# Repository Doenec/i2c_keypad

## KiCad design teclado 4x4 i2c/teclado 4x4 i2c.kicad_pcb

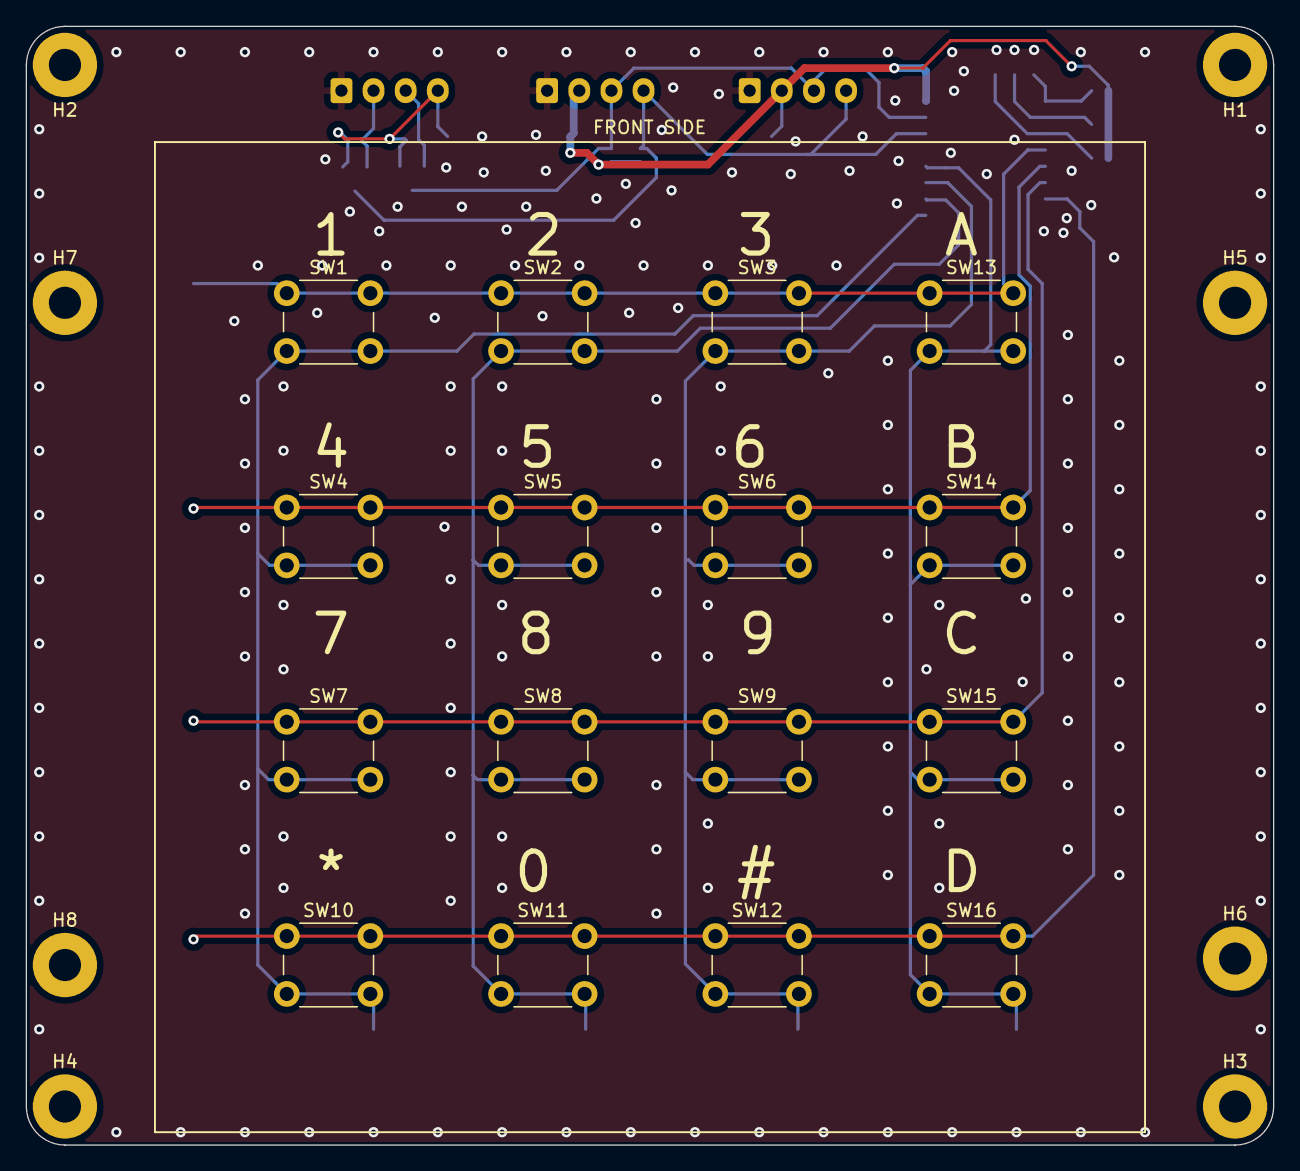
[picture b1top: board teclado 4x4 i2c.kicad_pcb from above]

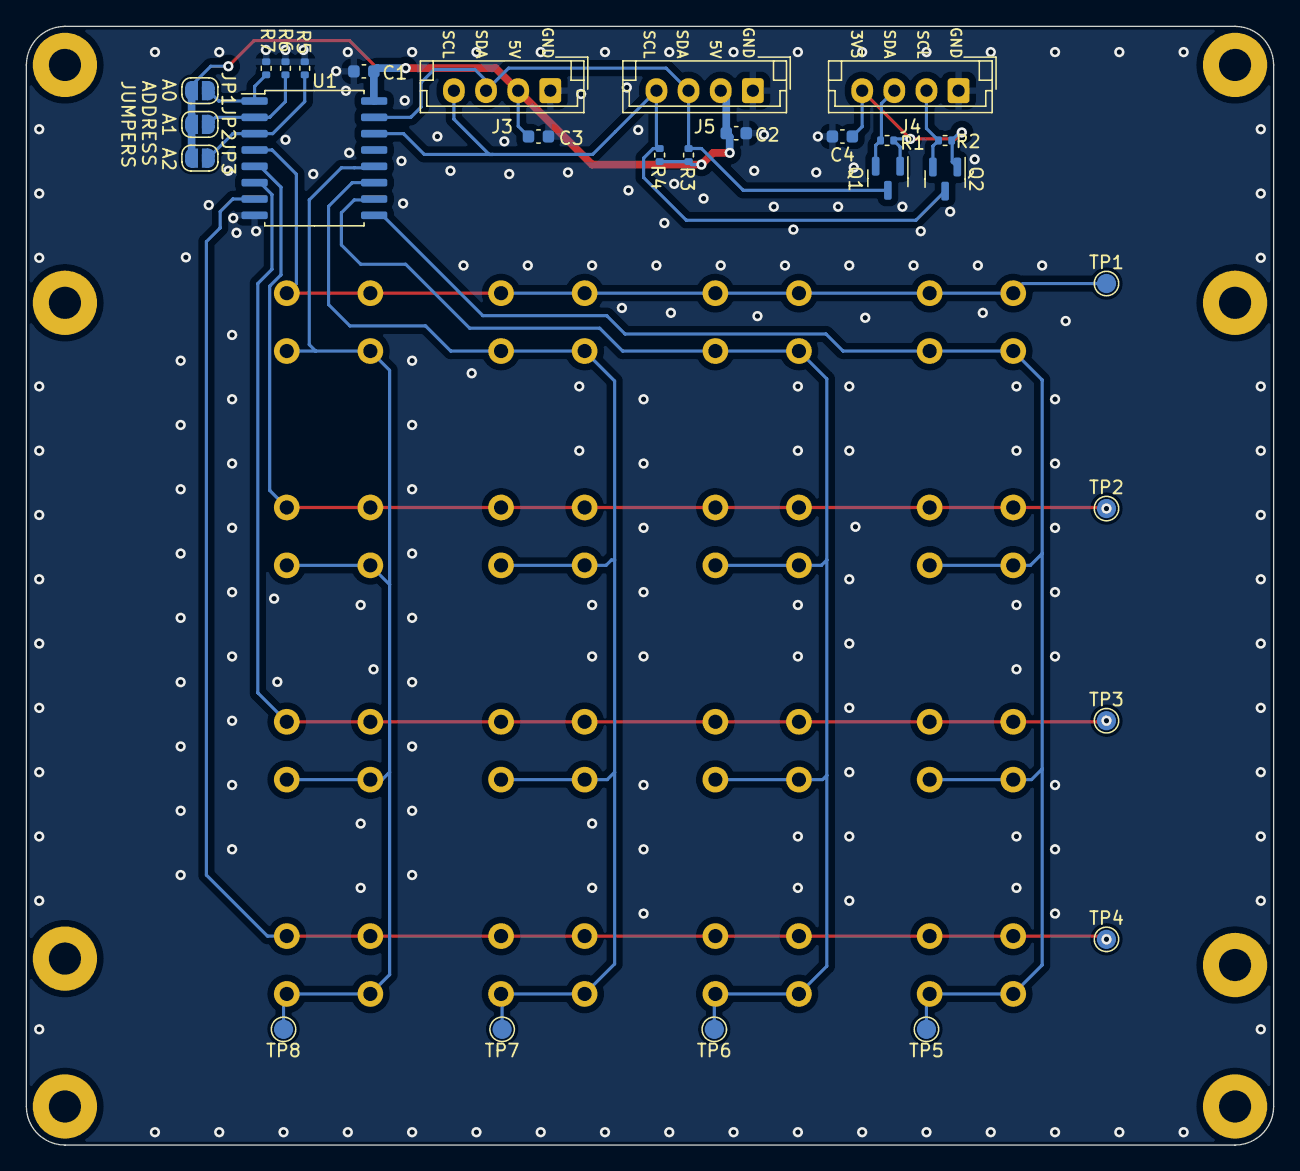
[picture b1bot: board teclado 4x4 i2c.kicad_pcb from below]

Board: 2 copper layers, 97.0 x 87.0 mm, 52 parts (28 on the bottom side), 18 nets.

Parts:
C1, C2, C3, C4: 100nF; C_0603_1608Metric
H1, H2, H3, H4, H5, H6, H7, H8: MountingHole; MountingHole_2.5mm_Pad
J3, J4, J5: I2C; JST_EH_B4B-EH-A_1x04_P2.50mm_Vertical
JP1, JP2, JP3: ADDR; SolderJumper-2_P1.3mm_Open_RoundedPad1.0x1.5mm
Q1, Q2: 2N7002; SOT-23
R1, R2, R3, R4, R5, R6, R7: 10K; R_0402_1005Metric
SW1: B1; SW_PUSH_6mm_H4.3mm
SW2: B2; SW_PUSH_6mm_H4.3mm
SW3: B3; SW_PUSH_6mm_H4.3mm
SW4: B4; SW_PUSH_6mm_H4.3mm
SW5: B5; SW_PUSH_6mm_H4.3mm
SW6: B6; SW_PUSH_6mm_H4.3mm
SW7: B7; SW_PUSH_6mm_H4.3mm
SW8: B8; SW_PUSH_6mm_H4.3mm
SW9: B9; SW_PUSH_6mm_H4.3mm
SW10: B*; SW_PUSH_6mm_H4.3mm
SW11: B0; SW_PUSH_6mm_H4.3mm
SW12: B#; SW_PUSH_6mm_H4.3mm
SW13: BA; SW_PUSH_6mm_H4.3mm
SW14: BB; SW_PUSH_6mm_H4.3mm
SW15: BC; SW_PUSH_6mm_H4.3mm
SW16: BD; SW_PUSH_6mm_H4.3mm
TP1, TP2, TP3, TP4, TP5, TP6, TP7, TP8: TestPoint; TestPoint_Pad_D1.5mm
U1: PCF8574; SOIC-16W_7.5x10.3mm_P1.27mm

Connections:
+3V3: C4.1, J4.4, Q1.1 (G), Q2.1 (G), R1.1, R2.1
+5V: C1.1, C2.1, C3.1, J3.2, J5.2, JP1.1 (A), JP2.1 (A), JP3.1 (A), R3.1, R4.1, U1.16 (VDD)
/A0: JP1.2 (B), R7.1, U1.1 (A0)
/A1: JP2.2 (B), R6.1, U1.2 (A1)
/A2: JP3.2 (B), R5.1, U1.3 (A2)
/PIN1: SW1.1, SW2.1, SW3.1, SW13.1, TP1.1, U1.4 (P0)
/PIN2: SW4.1, SW5.1, SW6.1, SW14.1, TP2.1, U1.5 (P1)
/PIN3: SW7.1, SW8.1, SW9.1, SW15.1, TP3.1, U1.6 (P2)
/PIN4: SW10.1, SW11.1, SW12.1, SW16.1, TP4.1, U1.7 (P3)
/PIN5: SW1.2, SW4.2, SW7.2, SW10.2, TP5.1, U1.9 (P4)
/PIN6: SW2.2, SW5.2, SW8.2, SW11.2, TP6.1, U1.10 (P5)
/PIN7: SW3.2, SW6.2, SW9.2, SW12.2, TP7.1, U1.11 (P6)
/PIN8: SW13.2, SW14.2, SW15.2, SW16.2, TP8.1, U1.12 (P7)
/SCL: J4.2, Q2.2 (S), R2.2
/SCL5: J3.4, J5.4, Q2.3 (D), R4.2, U1.14 (SCL)
/SDA: J4.3, Q1.2 (S), R1.2
/SDA5: J3.3, J5.3, Q1.3 (D), R3.2, U1.15 (SDA)
GND: C1.2, C2.2, C3.2, C4.2, J3.1, J4.1, J5.1, R5.2, R6.2, R7.2, U1.8 (VSS)

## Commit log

2024-01-02 Create info
    I want to share this in case be useful for someone. For a hardware developer, a very common problem when designing a new product is usually the case, the point at which the user must interact, what b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
    In this case I want a keyboard for an HMI interface, keyboard+display, it is easy to get 4x4 membrane keyboards on the internet with double-sided adhesive, however it is not very aesthetic and it is 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
    A couple of year ago I replaced one industrial membrane keyboard for plastic injection machines, th
